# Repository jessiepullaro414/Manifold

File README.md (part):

# Manifold — KiCad schematic + PCB

Companion KiCad project for "Manifold", an Arduino Nano inspired (pinout/
form-factor only — not an official Arduino product, and not Arduino-IDE
compatible) 12V-powered board built from automotive/high-temp-rated parts
for engine-bay environments.

## Opening it

Open `Manifold.kicad_pro` in KiCad 6, 7, or 8. Everything the schematic needs
(all symbols) is embedded in `Manifold.kicad_sch` itself — no external symbol
libraries required to open and view it.

Both the schematic and `Manifold.kicad_pcb` are kept in KiCad's **current
native format** (not just an older-but-compatible one) — see "File format" below.

J1's footprint (TE AMPSEAL 776180-1) lives in this project too —
[`fp-lib-table`](fp-lib-table) registers it under the library nickname
`TE_AMPSEAL_776180-1`, pointing at [`footprints/TE_AMPSEAL_776180-1.pretty/`](footprints/TE_AMPSEAL_776180-1.pretty)
via `${KIPRJMOD}` (KiCad's "this project's folder" variable) — so it resolves
automatically for anyone who opens this project, without depending on where
it was originally downloaded to.

Same pattern on the schematic side: [`sym-lib-table`](sym-lib-table) registers
this project's own custom parts under the nickname `Manifold`, pointing at
[`Manifold.kicad_sym`](Manifold.kicad_sym) (both regenerated by `build_schematic.py` -
don't hand-edit either). The schematic still embeds every symbol inline too
(so it opens/nets fine even without this), but a real external library file
is what lets KiCad's own "Add Symbol" browser find `Manifold:*` parts, and is
what a from-scratch `kicad-cli sch erc` needs to not flag every single part
as "library not included in configuration".

## Building it

[`build.py`](build.py) runs the whole real pipeline in order — schematic
generation, PCB placement, autorouting, DRC — the same four scripts
described in "Routing it" and "How the schematic is built" below, just
chained together:

```
python build.py                 # full pipeline
python build.py --skip-route    # skip the slow FreeRouting pass
```

## Checking it

[`run_drc.py`](run_drc.py) runs `kicad-cli pcb drc` against `Manifold.kicad_pcb`
(or any other `.kicad_pcb` passed as an argument) and prints a readable report from
the JSON it produces — unconnected-item count (expected on this unrouted board) plus
every other violation type, grouped, with the actual offending items and positions,
not just per-type counts. `build_pcb.py` also runs DRC as its own last step, but only
prints counts; reach for this when you need the detail behind one of those counts.

```
python run_drc.py
python run_drc.py path/to/other.kicad_pcb
```

`kicad-cli sch erc Manifold.kicad_sch` is the schematic-side equivalent.
It went from **388 violations to 4** during a real triage pass (not just a
recount) - see "Rotated-footprint pad shapes" below and
[[kicad-file-generation-gotchas]] for the technical detail on each fix:

- 259 `endpoint_off_grid` - every symbol placement now snaps to KiCad's
  0.05in (1.27mm) schematic grid.
- 70 `lib_symbol_issues` - added a real `Manifold.kicad_sym` + `sym-lib-table`
  entry (this project's custom parts were only ever embedded inline in the
  schematic before, with no external library file backing them - fine for
  KiCad to open/net-list, not fine for its "library not found" check or for
  inserting a fresh instance from the symbol browser).
- 25 `label_dangling` + 25 `no_connect_connected` - U1's 25 spare MCU pins
  now get a real no-connect flag instead of a same-named, inherently
  one-off local label.
- 3 `isolated_pin_label` - same fix, applied to 3 individually-unused pins
  elsewhere (U2's PG, U4's NC, J2's NC) via a new `('nc',)` `place()` mode.
- 1 `pin_to_pin` - J1's +5V/+3V3 pins were typed `power_out` (implying the
  *connector* generates power), conflicting with U4's real LDO output on
  the same net - retyped `passive` (a connector pin exposing a rail isn't
  a second source of it).

**The remaining 4 are genuine, expected ERC characteristics, not bugs** -
each one is ERC's pin-type-based "is this driven?" check failing to trace
through a passive network or off-board source, not a real missing
connection:

- `+5V`, `VDDA`, and U2's `VIN` each show `power_pin_not_driven` because
  their real source sits on the far side of an LC filter (L1), a ferrite
  (L2), or a MOSFET (Q1) - none of which have a `power_out`-type pin to
  point to, since ERC doesn't trace continuity through passives.
- J2's `SWCLK` shows `pin_not_driven` because it's genuinely driven
  off-sheet, by an external debug probe.

If you regenerate and see anything **other than these same 4**, treat it
as a real regression, not baseline noise.

## Buck feedback divider - a real bug found in final review

R2/R3 (U2's FB divider) used to be 10k/3.3k, solving TI's own formula
(`Vout = VREF x (RFBT/RFBB + 1)`, VREF = 1V nominal per LMR33630-Q1's
datasheet Section 8.2.2.3) to **~4.03V, not 5V** - a real, roughly-1V-low
output, not a rounding nitpick. This mattered because that rail is exposed
on J1 as a Nano-compatible +5V pin for **external peripherals** - anything
expecting real 5V plugged into it would have been under-powered or
malfunctioned outright, and it ate into U4's LDO dropout margin too.

Fixed by solving for RFBB with RFBT held at 10k: `10k / (5V/1V - 1) = 2.5k`,
using the nearest standard E96 value, **2.49k** - which is suspiciously
exactly TI's own worked-example RFBB (24.9k, for their 100k/24.9k 5V
divider) scaled down by 10x, suggesting 3.3k was a substitution/typo
somewhere rather than a deliberate choice. New value gives ~5.02V.

## File format

`kiutils` (the library both generators use) writes the older v6-era schema by
default — version `20211014`, generator `kiutils`, unquoted UUIDs, no
`generator_version` field. KiCad opens that fine, but flags schematics as
needing conversion, and that would reappear every time either generator
regenerates its file.

Fixed at the source rather than worked around: both generators' last step
shells out to `kicad-cli sch upgrade` / `kicad-cli pcb upgrade` — KiCad's own
real format converter — on the file they just wrote. If `kicad-cli` isn't
found on your machine, the scripts still finish and print a note — the files
just won't be pre-upgraded.

## The PCB: what's real, what's placeholder, what's routed

[`build_pcb.py`](build_pcb.py) reads the schematic + a fresh `kicad-cli`
netlist export and generates `Manifold.kicad_pcb`: every part's **real**
footprint (loaded from its actual `.kicad_mod` file, not reinvented), with
every pad assigned the net the schematic says it should have.

**What this does NOT do: route copper.** Placement gives a compact starting
point, but this is a netlist-correct *unrouted* board — the same state
"Update PCB from Schematic" leaves you in before you route it yourself.

**Placement is a real 2D bin-pack, not a row of parts.** All 27 small parts
go through a single **skyline bin-packer**: it maintains a height profile
across the board's full width (fixed by J1 regardless of how tightly the
small parts pack — J1 is 20-40x bigger than everything else, so it, not the
small parts, sets the real width floor) and places each part wherever it
produces the lowest resulting top edge — trying *every* part both unrotated
and rotated 90°, not just a designated subset. Since greedy bin-packing is
order-dependent (which part gets considered first changes the whole
resulting layout), `best_skyline_pack` runs it with 5 different orderings
(largest-area, longest-side, tallest, widest, largest-perimeter first) and
keeps whichever actually produced the shortest board — cheap to do exhaustively
for 27 parts, and not something a single fixed heuristic can guarantee on
its own. Board is currently ~83×61mm, down from an initial ~142×88mm
row-based layout.

**Diminishing returns, checked quantitatively, not just eyeballed:** after
this rewrite, a per-mm-column height profile across the packed region shows
almost the *entire* width already sitting at or near the maximum height —
not one big rectangular gap like before, but a tightly-filled, slightly
uneven skyline. That's because U1 (the MCU - at the time, still the
placeholder LQFP48 footprint; see "U1's pinout" below for why that was
wrong and what replaced it) was 10.3×10.3mm — by far the single biggest
part — and its own footprint+margin
already accounts for most of the packed region's height on its own,
regardless of what gets stacked around it. Forcing U1 to place *last*
instead of first (an explicit experiment, not a guess) made the board
*worse* (21.0mm packed height vs. 13.6mm) because all the good low spots
were already taken by the time U1 needed one. Clustering the MCU's own
decoupling caps (100nF/1uF) physically next to it is genuinely good
practice for the real routed board's signal integrity, but in this
bounding-box model it wouldn't shrink the board further, since U1's own
footprint already sets the height floor no matter which parts sit next to
it.

**A second real bug, found by comparing against a manual rearrangement:**
after seeing this layout, the user manually spread the small-parts grid out
further in the KiCad GUI and saved the file - reading those exact saved
coordinates back out (`(at x y angle)` per footprint, regex-extracted since
kiutils can't re-parse a KiCad-saved file - see gotchas doc) showed their
arrangement using ~78mm of width to reach ~10.8mm of height, meaningfully
shorter than the script's own ~74.6mm-wide, ~12.2mm-tall result at the time.
The packer was handing itself less room than it actually had: `pack_width`
was `j1_width - 2*BOARD_MARGIN`, reserving a *second* margin on the right of
the small-parts grid on top of the margin baked into `board_width`'s own
`max(used_w, j1_width) + 2*BOARD_MARGIN` formula. Since board width is
already going to be at least `j1_width + 2*BOARD_MARGIN` regardless, giving
the packer up to the full `j1_width` costs nothing as long as it stays
within that - fixed by setting `pack_width = j1_width` outright. A width
sweep (72-95mm) confirms `j1_width` is the actual area-minimizing choice for
this part mix, not an arbitrary pick: going wider trims a little more
height but grows board width faster than that saves. Board dropped from
83.4×62.4mm to 83.4×61.0mm on this fix alone - free, since the board was
already going to be at least that wide.

The manual arrangement still edges out the automatic packer somewhat
(~10.8mm vs ~12.2mm content height) - most likely because a human doing
this by eye can look at the whole board and backtrack, where the packer
commits to each part's position in one greedy left-to-right pass and never
revisits it. Closing that remaining gap would need a fundamentally
different search (backtracking or exhaustive), not just another ordering
heuristic - tried 8 orderings x 11 width targets in a grid search and the
result barely moved (60.92mm best vs 61.0mm), confirming this is a real
plateau for the current greedy-heuristic family, not a tuning oversight.

This replaced an earlier two-block design (a fixed "actives" column next to
a "caps" grid, sized by a pre-computed proportional-area split, with small
headers optionally dropped into whatever rectangle the split left over).
That design couldn't reach real density: caps are small and uniform and
pack far more efficiently per mm² than the actives, so even a "correct"
area-proportional width split still left the caps block *shorter* than the
actives column, and the leftover rectangle only fit parts that happened to
match its exact shape — real open board space stayed open, which is exactly
what got flagged when reviewing a render. A single shared skyline profile
lets any part drop into any low spot next to any neighbor, not just its own
block's slice, which is what actually closes gaps like that.

**A real rotation bug was caught verifying this one.** The 90°-CCW local
coordinate transform `(x,y) → (-y,x)` used everywhere rotation was needed —
in the packer's own placement math *and* in the pre-write overlap-check
verification, so both sides agreed with each other — turned out to be
backwards for KiCad's actual rotation direction (`(x,y) → (y,-x)`). Because
both sides used the same wrong formula, the script's own overlap assertion
never caught it — it was internally consistent, just wrong. It surfaced
instead as a real, tiny (0.015-0.18mm) pad-to-pad `clearance` and
`shorting_items` DRC violation between a rotated pin header (J3) and a
neighboring IC (U2), where the rotated header's far pads landed almost on
top of the IC's pads instead of facing away from it. Confirmed by manually
computing where kicad-cli's real DRC said those specific pads actually were,
which only matched the `(y,-x)` transform. This is the reason bugs like this
get caught by `kicad-cli`'s real DRC and not just the script's own geometry
checks — two internally-consistent code paths agreeing with each other is
not the same as either of them being correct.

Three more real bugs were found and fixed while doing this work:

- **Footprint bounding boxes were pad-only**, undercounting parts like J1 —
  a right-angle through-hole connector whose silkscreen/body outline extends
  well past its pad positions. This produced margins that looked fine on
  paper but caused real `silk_edge_clearance` and `courtyards_overlap` DRC
  errors at tight spacing. Fixed by including silkscreen graphics (lines,
  polys, arcs) in the bbox calculation, not just pads — after which margins
  could go back down to their intended tight values and every clearance
  error disappeared.
- **Every part showed as "REF\*\*"** in DRC reports and the 3D viewer,
  because only the silkscreen *text* was being updated (`fp.graphicItems`),
  not the separate `fp.properties["Reference"]`/`["Value"]` dict that KiCad's
  own tools (DRC, BOM, 3D view) actually read from. Fixed by setting both.
- **Every reference designator sat dead center on its own part, on top of
  its own pads** (`silk_over_copper` x58, `silk_overlap` x35 in
  `kicad-cli pcb drc` - see [run_drc.py](run_drc.py) below). Root cause:
  kiutils' `Footprint.properties` is a plain `{name: value}` string dict - it
  has no field for a property's position, layer, or font, so `to_file()` can
  only ever write a bare `(property "Reference" "REF")` token, discarding
  whatever real position the *source* library footprint had. `kicad-cli pcb
  upgrade` then fills in the missing fields using KiCad's own built-in
  default *for that property name* - Reference defaults to `(at 0 0 0)` on
  `F.SilkS`, i.e. dead center - which is fine on a normally-spaced board but
  guarantees overlap at this board's 2mm part spacing. (Value/Datasheet/
  Description bare properties *don't* show up as silkscreen violations,
  because KiCad's defaults for those names are F.Fab/hidden, not visible
  silkscreen - so this was specifically a Reference-designator problem, not
  a general "properties are broken" problem.) Fixed by patching the written
  file's bare `(property "Reference" "REF")` tokens - exact string
  replacement, not regex, since the one-line form kiutils writes is exactly
  known at that point in the script, before `pcb upgrade` ever touches the
  file - with a real per-part position (just clear of that part's own bbox,
  reusing the same `footprint_bbox()` already used for placement) and a
  0.8mm font sized for 2mm part spacing instead of KiCad's normal 1.27mm
  default. Went from 96 DRC violations to 3 (the remaining 3 are an
  unrelated `lib_footprint_mismatch` finding - local footprint copies
  differing slightly from their library originals, not a silkscreen issue).

## Layer stackup: 4 layers

`board.layers` now declares `F.Cu`, `In1.Cu`, `In2.Cu`, `B.Cu` (verified
present in the generated file after `pcb upgrade`). In1 as a solid GND pour
and In2 as a +5V/+3V3 pour is standard practice for a board with a switching
buck regulator on it — shorter return paths, better EMI — and this board
already has one, so 4 layers is a sensible default rather than an arbitrary
choice. Exact dielectric thickness/material is left at KiCad's defaults; set
those in Board Setup if you have fab-specific requirements.

**The planes are now real, not just planned.** `route_board.py`'s
`add_and_fill_zones()` pours a solid **GND zone on In1.Cu** and a solid
**+3V3 zone on In2.Cu** (the primary MCU supply rail now that U1 runs
entirely on 3.3V — see "The MCU" below; +5V stays a normal routed trace,
since it's the lower-current Nano-compatibility rail feeding just J1's +5V
pin and the LDO input, not something else on this board depends on for a
low-impedance return path the way the buck regulator's GND loop does).

**Zones are added AFTER routing, not before — that ordering is load-bearing,
not a style choice.** The first attempt added the zone outlines in
`build_pcb.py`, *before* handing the board to FreeRouting, on the theory
that its Specctra DSN "plane" mechanism would let the autorouter treat
those layers as pre-claimed and route everything else around them. That
backfired two different ways:

1. **It made this already-tight board measurably harder to autoroute.** A
   solid zone covering an entire inner layer removes that layer's normal
   "just drop a via here" flexibility everywhere on the board, not only
   where the plane's own net actually needs it — and this board has a
   0.5mm-pitch 64-pin LQFP and a similarly tight VQFN-12 with very little
   room to spare already. Runs that reliably hit 0 unrouted nets before
   zones existed started leaving 1-4 stuck on the same few tight spots
   (U2's exposed-pad-to-pin connection, some U1-to-J1 nets) with zones
   present pre-route.
2. **Worse: FreeRouting would report "100% routed" while `run_drc.py` still
   found real "missing connection" findings** between GND/+3V3 pads (e.g.
   J1's THT pins) and the zone itself. The router had skipped drawing an
   explicit trace/via to some pads, assuming the plane would cover them —
   but the *actual* fill polygon, computed afterward and cleared around
   every other net's copper, didn't always reach every such pad. FreeRouting's
   own self-report and KiCad's real DRC were checking two different things,
   and only the second one is trustworthy — another instance of this
   project's running theme that a tool's own "success" claim isn't
   verification.

The fix: route the whole board as ordinary traces first — the same simple,
reliable regime that got 0 unconnected items before any zones ever existed —
and only *then* add the zones as purely additive copper on top of an
already-100%-connected board. Any GND/+3V3 trace or via the zone happens to
overlap becomes redundant (harmless), not the *only* connection, so there's
no longer any way for a pad to end up "connected only via a plane that
doesn't quite reach it." Pad connections are solid (`ZONE_CONNECTION_FULL`),
not thermal-relief spokes, for the same reliability reason — no spoke
geometry to fail, and this board isn't hand-soldered at a scale where
thermal relief's easier-rework benefit outweighs connection certainty.

**One more real bug along the way, a KiCad Python-scripting one, not a
design one:** filling both zones (different layers) in a single `pcbnew`
process reliably **segfaults** on the subsequent `board.Save()` — confirmed
directly by isolating each step (adding both zones: fine; filling both:
fine; only `Save()` afterward crashes, every time, only with two
different-layer zones present together). One zone filled and saved alone
never crashes. Root cause looks like a real threading/state bug in this
KiCad build's zone filler under scripting, not something to tune around via
zone settings — worked around by doing each zone in its own **separate**
`python.exe` subprocess (load → add one zone → fill → save), so the second
zone's process loads a file that already has the first zone's completed
fill baked in, and the two fills are never in memory together.

## Branding: the JessiesCars logo on B.SilkS

`build_pcb.py` places a real vector logo (badge + winged mark) on the back
silkscreen, sourced from [`both.kicad_sym`](both.kicad_sym) — a
`bitmap2component`-generated schematic symbol (29 polylines, ~1450 points,
traced from the real artwork, not anything this script invents). B.SilkS is
otherwise completely empty (nothing's mounted on the back), so it's placed
in J1's own footprint "shadow" — J1's bbox has a tall lower region below its
3 pad rows (its plastic housing outline) with zero pads or drills in it,
genuinely clear space rather than just visually-empty space a THT pad barrel
would poke through.

**Two coordinate-transform bugs, both caught by literally looking at the
render, not by DRC** (DRC has no way to know a logo is upside down or
backwards — this is a visual-correctness class of bug, not an electrical
one):

1. **Symbol space is Y-up, PCB board space is Y-down** — the exact same
   convention gotcha `build_schematic.py` already documents for placing
   symbol pins onto the sheet, easy to forget applies here too since
   `both.kicad_sym` is *also* a symbol-space file. Missing this flip put the
   whole logo upside down on the first attempt.
2. **A back-layer shape's stored coordinates are NOT auto-mirrored by
   KiCad** — only *text* gets a `mirror` flag (`Justify(mirror=True)`, see
   `kicad-file-generation-gotchas`); a plain polygon's points are used
   as-is, so artwork authored in normal (front-view) orientation reads
   backwards once the physical board is flipped over to view the back. Text
   needs the flag; polygons need their X coordinates negated by hand before
   placing, since they have no equivalent flag to set.

Both flips are real and both apply *together* (not either/or) — applying
only one produces a result that's wrong in a *different*, less obviously
"just mirrored" way (a 180° rotation, not a clean left-right flip), which is
exactly what the first attempt looked like: legible-ish but wrong letters
("CARZ" for "CARS"), not obviously backwards at a glance. Fixed by negating
*both* X and Y before scaling/placing. Verified by rendering the back side
(`kicad-cli pcb render --side bottom`) and reading the actual wordmark, not
just checking DRC — DRC-clean and visually-correct are different checks
here.

Same `gr_poly` gotcha as `gr_text` on the uuid front: kiutils' `tstamp`
field writes an unquoted `(tstamp xxxx)`, not the quoted `(uuid "xxxx")` a
real KiCad-written `gr_poly` has, and `kicad-cli` segfaults loading the file
without it — patched post-write, same pattern as the Reference-label and
credit-text fixes before it.

## Routing it

[`route_board.py`](route_board.py) routes the board with
[FreeRouting](https://github.com/freerouting/freerouting), the same way most
KiCad users do it manually: export a Specctra `.dsn`, autoroute it, import
the resulting `.ses` back, then pour the GND/+3V3 zones on top. Four steps,
run headless:

```
python route_board.py
python run_drc.py
```

1. **Export** — `pcbnew.ExportSpecctraDSN()`, called through KiCad's own
   *bundled* Python (`C:\Program Files\KiCad\10.0\bin\python.exe`, which has
   the real `pcbnew` module — different from the Python that runs the rest
   of this project's scripts). This is KiCad's real, tested exporter, not a
   reimplementation — `kicad-cli` doesn't expose DSN export at all (checked;
   its `pcb export` subcommand list has no `dsn`/`specctra` option), but the
   underlying scripting API does, and it's fully headless.
2. **Route** — `java -jar tools/freerouting-2.2.4.jar -de ... -do ... -mp 60
   -oit 0 --gui.enabled=false`. Requires Java (this project uses Eclipse
   Temurin 25 JRE) and the FreeRouting jar (57.8MB, not committed — see
   below).
3. **Import** — `pcbnew.ImportSpecctraSES()`, same bundled-Python mechanism,
   writes the routed tracks/vias back into `Manifold.kicad_pcb` and
   saves it.
4. **Pour zones** — GND on In1.Cu, +3V3 on In2.Cu, added and filled *after*
   routing (not before — see "Layer stackup" above for why that ordering
   matters and the real bugs skipping it caused), each in its own separate
   `python.exe` subprocess (also explained above — filling both in one
   process segfaults on save).

**Setup** (one-time): install a JRE, and download
[`freerouting-2.2.4.jar`](https://github.com/freerouting/freerouting/releases/tag/v2.2.4)
into `tools/`. The **jar**, not the installer — FreeRouting's own docs
specify the jar for headless/CLI use; the installers are for interactive
use only.

**Current result**: FreeRouting routes all 47 nets (103 pin-to-pin
connections, after U1's real 64-pin pinout replaced the old unwired
placeholder — see "U1's pinout" below) in 15-30 seconds — `run_drc.py`
confirms 0 unconnected items, same handful of pre-existing
`lib_footprint_mismatch` findings as before, nothing routing-related.

**The autorouter isn't perfectly deterministic run-to-run** — occasionally
it'll settle for 1-4 nets unrouted and stop (its own plateau-detection
gives up when a pass makes no further progress), rather than reaching 0
every single time. When that happens, just re-run `python route_board.py`
from a fresh `python build_pcb.py` (not on top of the partially-routed
board — re-routing incrementally on top of a stuck partial state hits the
same plateau again, since nothing about the board actually changed).
A second full-from-scratch attempt has reliably reached 0 unrouted so far.

**The inner layers are real planes now, not general routing layers** — see
"Layer stackup" above for the GND/+3V3 zone pours and the real bugs (a
routing-reliability regression and a scripting segfault) that showed up
getting there.

**U1 is fully wired now — no exceptions.** Earlier revisions of this board
left every one of U1's pads without a net, because its schematic pin numbers
were an unverified generic placeholder that didn't reflect any real chip's
actual pinout — wiring them to the real footprint's pads by number
coincidence would have produced confidently *wrong* connections, worse than
no connections at all. That's resolved: U1's pin numbers are now the real,
NXP-Reference-Manual-verified S32K144 64-pin LQFP pinout (see "U1's pinout"
above), so it gets normal net assignment like every other part.

Verified after generation, every time: no two footprints' bounding boxes
overlap, every net has the same pin count on the PCB as in the schematic (47
nets currently), and a real `kicad-cli pcb drc` pass comes back with zero
connectivity/footprint errors (only a benign "doesn't match library copy"
metadata nag on a handful of footprints that's just an artifact of embedding
them via script — re-running "Update Footprints from Library" in pcbnew
clears it).

**A real bug caught and fixed during this verification:** the AMPSEAL
connector's downloaded footprint uses KiCad's legacy *unquoted* pad-number
syntax, which `kiutils` parses as a Python `int` — silently failing every
net-lookup for that footprint (all pad numbers are stored as strings
everywhere else) until the lookup was fixed to normalize types. Before the
fix, J1 looked structurally fine (right pad count, right pattern) but
carried zero of its real net assignments.

## How the schematic is built

Every part uses a **generic placeholder symbol**: a rectangle body with pins.
For most parts (see below), the pin count/numbers/names are now **real**,
verified against actual manufacturer datasheets — not generic filler.

Connectivity uses three mechanisms, matching normal schematic practice:

- **Drawn wires** for the main signal flow: the 12V power chain (fuse →
  reverse-battery FET → buck), the MCU↔J1 signal bus, and the crystal.
- **Power symbols** (+5V, +3V3, GND, VIN) at every power-net connection point.
  Power nets deliberately never use local labels — mixing local labels with
  power symbols splits nets in KiCad.
- **Local labels** for shared or non-Nano-pinout signals: UART sharing D0/D1,
  the FB divider, VDDA/AREF/OSC taps, VCAP/BOOT_CAP for the two ICs that need
  an external charge-pump/bootstrap cap.

**Before you route a board from this:** swap the placeholder symbols for real
library symbols (matching what's now real about the footprints/pinouts) and
give it a visual tidy-up. Treat this as a correct **netlist and BOM skeleton**,
not a finished, review-ready schematic.

## Sections on the sheet

| Section | Refs | Notes |
|---|---|---|
| Power input & protection | F1, Q1, U3, D1, C1, C10 | Fuse, reverse-battery ideal-diode + FET, TVS clamp, charge-pump cap |
| 5V buck regulator | U2, L1, C2, R2, R3, C11, C12 | 12V (9–40V transient) → 5V. Now exists **only** for a Nano-compatibility 5V pin on J1 — the MCU itself no longer runs on this rail |
| 3.3V LDO | U4, C3 | Steps 5V → 3.3V, which is now the **primary MCU supply**, not just a spare pin |
| MCU core | U1, Y1, C4–C5, L2, R1 | NXP S32K144 automotive (real AEC-Q100 qualification), 8MHz placeholder crystal, reset pull-up, VDDA ferrite-filtered |
| Connectors | J1, J2, J3 | J1 = full Nano-pinout I/O on a **TE AMPSEAL 776180-1** (35-pos, right-angle, sealed), J2 = **SWD** (SWDIO/SWCLK/RESET), J3 = UART (shares D0/D1) |

Full component rationale lives in the design-spec document delivered
alongside this file — this schematic is the follow-through on that spec.

## The MCU: from ATmega328P → STM32 → NXP S32K144 (and losing "Arduino IDE")

This went through two real revisions, both driven by things that turned out
not to be true on closer inspection:

1. **ATmega328P → STM32L452xx**, because no automotive-qualified 5V-native
   Arduino-ish chip exists. This looked right at the time.
2. **STM32L452xx → NXP S32K144**, because it turned out mainstream STM32
   (Cortex-M) parts have **no AEC-Q100 qualification at all** — confirmed via
   ST's own community forum: *"not a single device in the standard STM32
   family meets the AEC-Q specs."* ST's real automotive 32-bit line (SPC5) is
   Power Architecture, not ARM, not Arduino-anything.

NXP's S32K1 family is genuinely AEC-Q100 qualified Arm Cortex-M4F. But:

- **This means giving up Arduino IDE support entirely** — not just the
  STM32duino alias-mapping caveat from before. NXP's own S32K144 EVB
  documentation is explicit: *"the NXP S32K144 is NOT natively supported by
  the Arduino IDE... development requires the dedicated S32 Design Studio IDE
  and the S32 Software Development Kit."* The "Arduino UNO pin layout"
  compatibility NXP markets is **physical only** — no `digitalWrite()`,
  `Serial`, or sketch-based workflow exists for this chip. Programming is via
  NXP's Eclipse-based IDE and an AUTOSAR-style SDK — a genuinely different,
  more automotive-industrial development workflow.
- **Still 3.3V logic, not 5V** — same consequence as before, unrelated to
  which 3.3V-logic chip is on the board. J1's dedicated +5V pin (unconnected
  to the MCU) remains the only genuine 5V on the board.

### U1's pinout: from placeholder to real, verified, and fully wired

**The 48-pin LQFP placeholder used until now was not just unverified — it
was wrong.** The S32K144 does not come in a 48-pin LQFP package at all.
Confirmed three independent ways against NXP's own S32K1xx Series Reference
Manual (Rev 8, 06/2018): S32K144's own pin-mapping sheet only has columns
for 64-LQFP/100-LQFP/100-BGA; sibling part S32K142's sheet is the same;
48-pin LQFP is a real NXP package, but it belongs to the smaller
S32K116/S32K118 sub-family (Cortex-**M0+**, not the M4F this board was
chosen for). **The real minimum package for S32K144 is 64-pin LQFP.**

Every earlier attempt at this (this session and prior ones) failed to fetch
the "pin table" because it isn't in the datasheet or Reference Manual's
visible text at all — NXP ships it as a spreadsheet
(`S32K144_IO_Signal_Description_Input_Multiplexing.xlsx`) embedded as a PDF
**file attachment** inside the Reference Manual, not as text or a table on
any page. Regular PDF text extraction (`pdftotext`, WebFetch) can't see it.
Pulled out directly with `pypdf`'s attachment API once a mirror that wasn't
blocking the download was found (Farnell, not Mouser/NXP/community.nxp.com —
all three of those still 403/timeout).

With the real, verified 64-pin table in hand, **U1 is now fully wired** —
no more placeholder, no more unwired pads:

- **58 real GPIO pins**, of which 5 keep their real default (reset-state)
  function matching how this board already used them: pin 11 (PTB7/EXTAL)
  and 12 (PTB6/XTAL) → the crystal, pin 62 (PTC4/SWD_CLK) and 64
  (PTA4/SWD_DIO) → the SWD header, pin 63 (PTA5/RESET_b) → reset.
- **VREFH (pin 9, the real ADC voltage-reference pin) goes to J1's AREF** —
  not a placeholder GPIO. AREF on a real board should reach the actual
  reference input, and now it does.
- **D0–D19 (20 pins, up from the placeholder's 14)** and **A0–A7 (8 pins,
  specifically chosen from the 27 real GPIO pins with a genuine `ADCn_SEx`
  alternate function — "analog in" is a real capability here, not just a
  name carried over from Arduino)**. D14–D19 are new: J1's 6 previously-spare
  pins now carry them, so **all 35 of J1's positions are used, zero spare**
  (see "Nano-pinout I/O" below).
- The other **25 free GPIO pins** aren't wired to anything — J1 has no more
  physical positions left for them — and are marked `no_connect` on the
  schematic with their real pin numbers, not placeholder ones.
- **U1's PCB footprint is now the real bundled KiCad
  `Package_QFP:LQFP-64_10x10mm_P0.5mm`**, replacing the placeholder
  `LQFP-48_7x7mm_P0.5mm`. `build_pcb.py`'s old "leave U1 unwired, its pin
  numbers might be wrong" special case is gone — U1 gets normal net
  assignment like every other part now, because its pin numbers are real.

SWDIO/SWCLK were always real, universal Arm Cortex-M debug signals
regardless of vendor — that part of the old placeholder note held up.
There is no BOOT0-style pin on this family (that was STM32-specific).

## Four parts that got real, verified pinouts this session

While researching the MCU footprint, real datasheet research (TI and
Nexperia PDFs, pulled and parsed directly) turned up genuine errors in four
other parts — now fixed with real pin numbers, not generic placeholders:

- **U2 (buck regulator):** LMR33630-Q1's real package is **VQFN-HR-12
  ("RNX0012C", 2×3mm body, ≤1mm height)** — it was never offered in
  HTSSOP-16 at all, which is what the schematic originally specified. Real
  12-pin table verified against TI's datasheet Table 5-1: symmetric
  VIN/PGND pairs for EMI cancellation, NC(3) tied to SW per the datasheet's
  own instruction, BOOT(4) needs a cap to SW (added: C11), VCC(5) is an
  internal 5V rail needing its own decoupling cap (added: C12), PG(8)
  unused here. **This package has no exposed pad at all** — an earlier
  version of this file (and the schematic) had a 13th "EP" pin tied to
  GND, which was wrong and has been removed; TI's own Pin Functions table
  has no EP row for this variant. The footprint is custom-built (not a
  bundled KiCad part, and not the wrong-sized 4×4mm placeholder used
  earlier) — see [`build_u2_footprint.py`](build_u2_footprint.py) for how
  the land pattern was derived directly from TI's package drawing
  (4225021/C, 05/2022) and [`footprints/TI_RNX0012C_VQFN-HR.pretty/`](footprints/TI_RNX0012C_VQFN-HR.pretty)
  for the result. This package's pin layout is genuinely irregular — 4
  pins down each side, 3 along the bottom, and one larger single pin (SW)
  on its own at the top — not a simple 3-per-side QFN, so it's worth
  opening the footprint in KiCad's footprint editor at least once before
  fab to see the real shape.
- **U3 (ideal-diode controller):** the schematic originally specified
  **LM74670-Q1, which turned out to be the wrong part** — that's TI's
  controller for alternator/rectifier diode emulation, not reverse-battery
  protection. The correct, purpose-built part is **LM74700-Q1** ("Low IQ
  Reverse Battery Protection Ideal Diode Controller"), real 6-pin SOT-23
  (DBV) package, real pinout verified against TI's datasheet. It also needs
  an external charge-pump capacitor across VCAP and ANODE that the schematic
  never had — added as C10, now confirmed at **100nF** against TI's actual
  design guidance (section 10.1.1.2.3): "VCAP: Minimum 0.1uF is required;
  recommended value of VCAP(uF) >= 10 x CISS(MOSFET)(uF)". Q1's real Ciss
  (450pF for the current part, PMV37ENEA, per Nexperia's datasheet) makes
  the formula's own figure (4.5nF) far smaller than the flat 0.1uF minimum,
  so the minimum governs - matching TI's own 12V-battery-protection example
  circuit exactly. The original 10nF value was 10x under TI's stated
  minimum, not just an unconfirmed guess.
- **U4 (LDO):** real candidate **TLV733P-Q1** (AEC-Q100) is 5-pin SOT-23
  (DBV), not the 3-pin package originally assumed. Real pinout verified
  against TI's datasheet.
- **Q1 (MOSFET), resolved with a real part swap:** the original candidate,
  **Nexperia PMV230ENEA** (AEC-Q101, SOT-23, pinout Gate=1/Source=2/Drain=3,
  verified against Nexperia's datasheet), derated to 0.9A at 100°C ambient -
  genuinely *below* F1's fuse rating at the time (originally 1A - see "F1"
  below for why it's now 2A), meaning the MOSFET could overheat at F1's
  normal, non-fault operating current, not just a thin margin. Replaced with
  **PMV37ENEA**: same SOT-23/TO-236AB package, same pinout, same 60V VDS (no
  TVS/clamping rework needed) - but RDSon of 37-49mOhm (vs 176-222mOhm)
  gives 3.5A@25°C / **2.5A@100°C**, comfortably above F1's rating with real
  margin either way (1A originally, 2A now), AEC-Q101 qualified, -55 to
  175°C range. One minor, honestly-noted mismatch: PMV37ENEA's max Vth
  (2.7V) is slightly above LM74700-Q1's own stated preference ("2V to 2.5V
  maximum") for its light-load regulation scheme - not a hard limit, worth
  a bench check at light load before final part lock.

A real geometry bug was also caught and fixed while wiring these up: a GND
power connection's extra riser wire landed exactly on a neighboring pin's own
stub, silently shorting that pin's real net onto GND. Caught via `kicad-cli`
netlist diff (an entire net had vanished), fixed, and now checked
automatically on every regeneration (`build_schematic.py` asserts no two
different net labels ever land on the same coordinate).

## AEC-Q100 / Q101 / Q200 grade key

Every part's `Value` field on the sheet is tagged with its actual automotive
qualification:

- **Q100 G1** = AEC-Q100 Grade 1 (−40°C to 125°C) for *integrated circuits*:
  U2 (buck), U3 (ideal-diode controller), U4 (LDO) — all TI, all verified.
  U1 (MCU) carries **AEC-Q100** (no grade suffix, since the exact grade for
  this NXP family wasn't independently confirmed this session).
- **Q101** = AEC-Q101, for *discrete semiconductors*: Q1 (MOSFET), D1 (TVS).
- **Q200** = AEC-Q200, for *passives*: Y1, C1–C13, R1–R3, L1, L2.
- **F1 (fuse) and J1–J3 (connectors) intentionally have no AEC-Q tag** — those
  categories aren't covered by the AEC-Qxxx family at all; they're qualified
  against their own standards (SAE J2077 / ISO 8820-3 for F1's real Littelfuse
  297 MINI automotive blade fuse, connector-specific automotive standards for
  J1-J3). Don't read the missing tag as an oversight.

## Footprints (for "Update PCB from Schematic")

Every footprint field is a real KiCad library reference, checked directly
against the actual `.kicad_mod` files (not just typed from memory):

- F1: Keystone 3568 Mini blade fuse holder (`Fuse:Fuseholder_Blade_Mini_Keystone_3568`,
  bundled directly in KiCad, 3D model included) - a traditional, physically
  replaceable automotive blade fuse, not a soldered-down SMD fuse. See
  "F1: traditional blade fuse" below for why.
- U2: real, custom-built VQFN-HR-12 footprint (`TI_RNX0012C_VQFN-HR:TI_RNX0012C_VQFN-HR-12_2x3mm_P0.5mm`)
  — see above and [`build_u2_footprint.py`](build_u2_footprint.py).
- U3: real SOT-23-6 (bundled).
- U4: real SOT-23-5 (bundled).
- Q1: real SOT-23 (bundled).
- J2: `Tag-Connect_TC2030-IDC-NL...` — note the hyphen KiCad's real file uses
  (`Tag-Connect`, not `TagConnect`).
- **J1 is fully resolved, including a real dimensional check:** **TE
  Connectivity AMPSEAL 776180-1** — 35-position, 3-row, 4mm pitch,
  right-angle through-hole, sealable, −40°C to 125°C / IP67. Its footprint
  was downloaded from
  [SnapEDA](https://www.snapeda.com/parts/776180-1/TE+Connectivity/view-part/)
  and copied into [`footprints/TE_AMPSEAL_776180-1.pretty/`](footprints/TE_AMPSEAL_776180-1.pretty)
  for project portability. Checked directly against TE's own real customer
  drawing (`ENG_CD_776180_J.pdf`, fetched from `te.com`'s document-delivery
  system, sheet 2's "RECOMMENDED P.C. BOARD LAYOUT" - a real, dimensioned
  engineering drawing, not the datasheet's summary page): pin drill
  (Ø1.75mm), pin pitch (4mm), row stagger (2mm), mounting-hole diameter
  (Ø2.85mm), and mounting-hole-to-mounting-hole span (57mm) all matched the
  downloaded footprint exactly. **One real, genuinely wrong dimension was
  found and fixed**: the two non-plated mounting holes were 0.5mm off in Y
  (at 4.5mm instead of 4.0mm) - TE's drawing shows them sitting exactly
  in-line with the middle pin row, not offset from it. Confirmed via the
  PDF's own vector geometry (mounting hole's crosshair falls exactly on the
  middle row's construction line), not just eyeballing the rendered page.
  Fixed directly in `TE_1-776180-1.kicad_mod` (a downloaded static library
  asset, not something this project's scripts generate from scratch, so a
  direct edit - not a generator script - is the right fix here).
- **U1 is fully resolved too** — see "U1's pinout" above. The footprint
  *was* the issue here (LQFP48 isn't a real S32K144 package at all), not
  just the pin-to-net mapping; both are fixed now, using the real
  Reference-Manual-verified 64-pin LQFP pinout and footprint.

## 3D models

Four parts had no 3D model showing in KiCad's 3D viewer, for three
different reasons:

- **J1** simply never had one — its footprint was a bare SnapEDA download
  (2D only). Fixed with a real manufacturer STEP file
  ([`1-776180-1.step`](footprints/TE_AMPSEAL_776180-1.pretty/TE_1-776180-1.step)),
  downloaded and supplied directly by the user, wired into
  `TE_1-776180-1.kicad_mod` with a `${KIPRJMOD}`-relative `(model ...)`
  block (same portability pattern as the footprint itself).
- **F1** (originally the Littelfuse NANO2 SMD fuse) had this same missing-
  model problem — its `(model ...)` reference pointed at
  `${KICAD10_3DMODEL_DIR}/Fuse.3dshapes/Fuse_Littelfuse-NANO2-451_453.step`,
  which doesn't actually exist in this KiCad 10 install (checked directly:
  the real `Fuse.3dshapes` folder has 28 files, none of them this one) - a
  real packaging gap in the bundled library, not a project bug. Moot now:
  F1 was later replaced entirely with a traditional Mini blade fuse holder
  (see "F1: traditional blade fuse" below) whose bundled model genuinely
  exists in this install, so no placeholder/workaround is needed for F1
  anymore at all.
- **U2**'s custom-built footprint (see above) never had a model at all,
  since it was hand-built from a datasheet rather than downloaded from a
  library that would normally ship one alongside it.
- **J2** (Tag-Connect TC2030-IDC-NL) is not a bug and got no model: its
  real footprint (checked directly against the bundled `.kicad_mod`) is 6
  bare `connect`-type pads plus 2 non-plated locating holes and nothing
  else — `attr exclude_from_pos_files exclude_from_bom` even marks it as
  not a placeable, orderable part. The actual Tag-Connect hardware is a
  detachable pogo-pin cable head that's never mounted on the assembled
  board, so there's genuinely no physical body to model here.

U2's placeholder ([`build_3d_models.py`](build_3d_models.py), using
[`cadquery`](https://cadquery.readthedocs.io/) to write a real STEP file, not
just a KiCad-only format) is a real-dimension bounding box, not
manufacturer-exact art — good enough for a 3D-viewer sanity check and
clearance reasoning, not a photorealistic BOM render:

- U2: 2.0 x 3.0 x 1.0mm, the same real TI package-drawing dimensions
  already used to build the 2D footprint (`build_u2_footprint.py`).

## Rotated-footprint pad shapes (real KiCad/kicad-cli characteristic, not a script bug)

Building U2's real, densely-pitched (0.5mm) VQFN-HR footprint surfaced a
subtle, reproducible characteristic of how KiCad 10.0.4 handles a footprint
placed at a 90° rotation: the footprint's overall placement rotation (its
`(at x y 90)`) correctly rotates every pad's *position*, but does **not**
carry through to each pad's own *shape* for rendering or DRC purposes unless
that pad also has its own local rotation angle set to match. Confirmed with
a from-scratch, hand-written two-pad test footprint (no `kiutils` involved
at all) placed once at 0° and once at 90°: only the 90° copy showed a false
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
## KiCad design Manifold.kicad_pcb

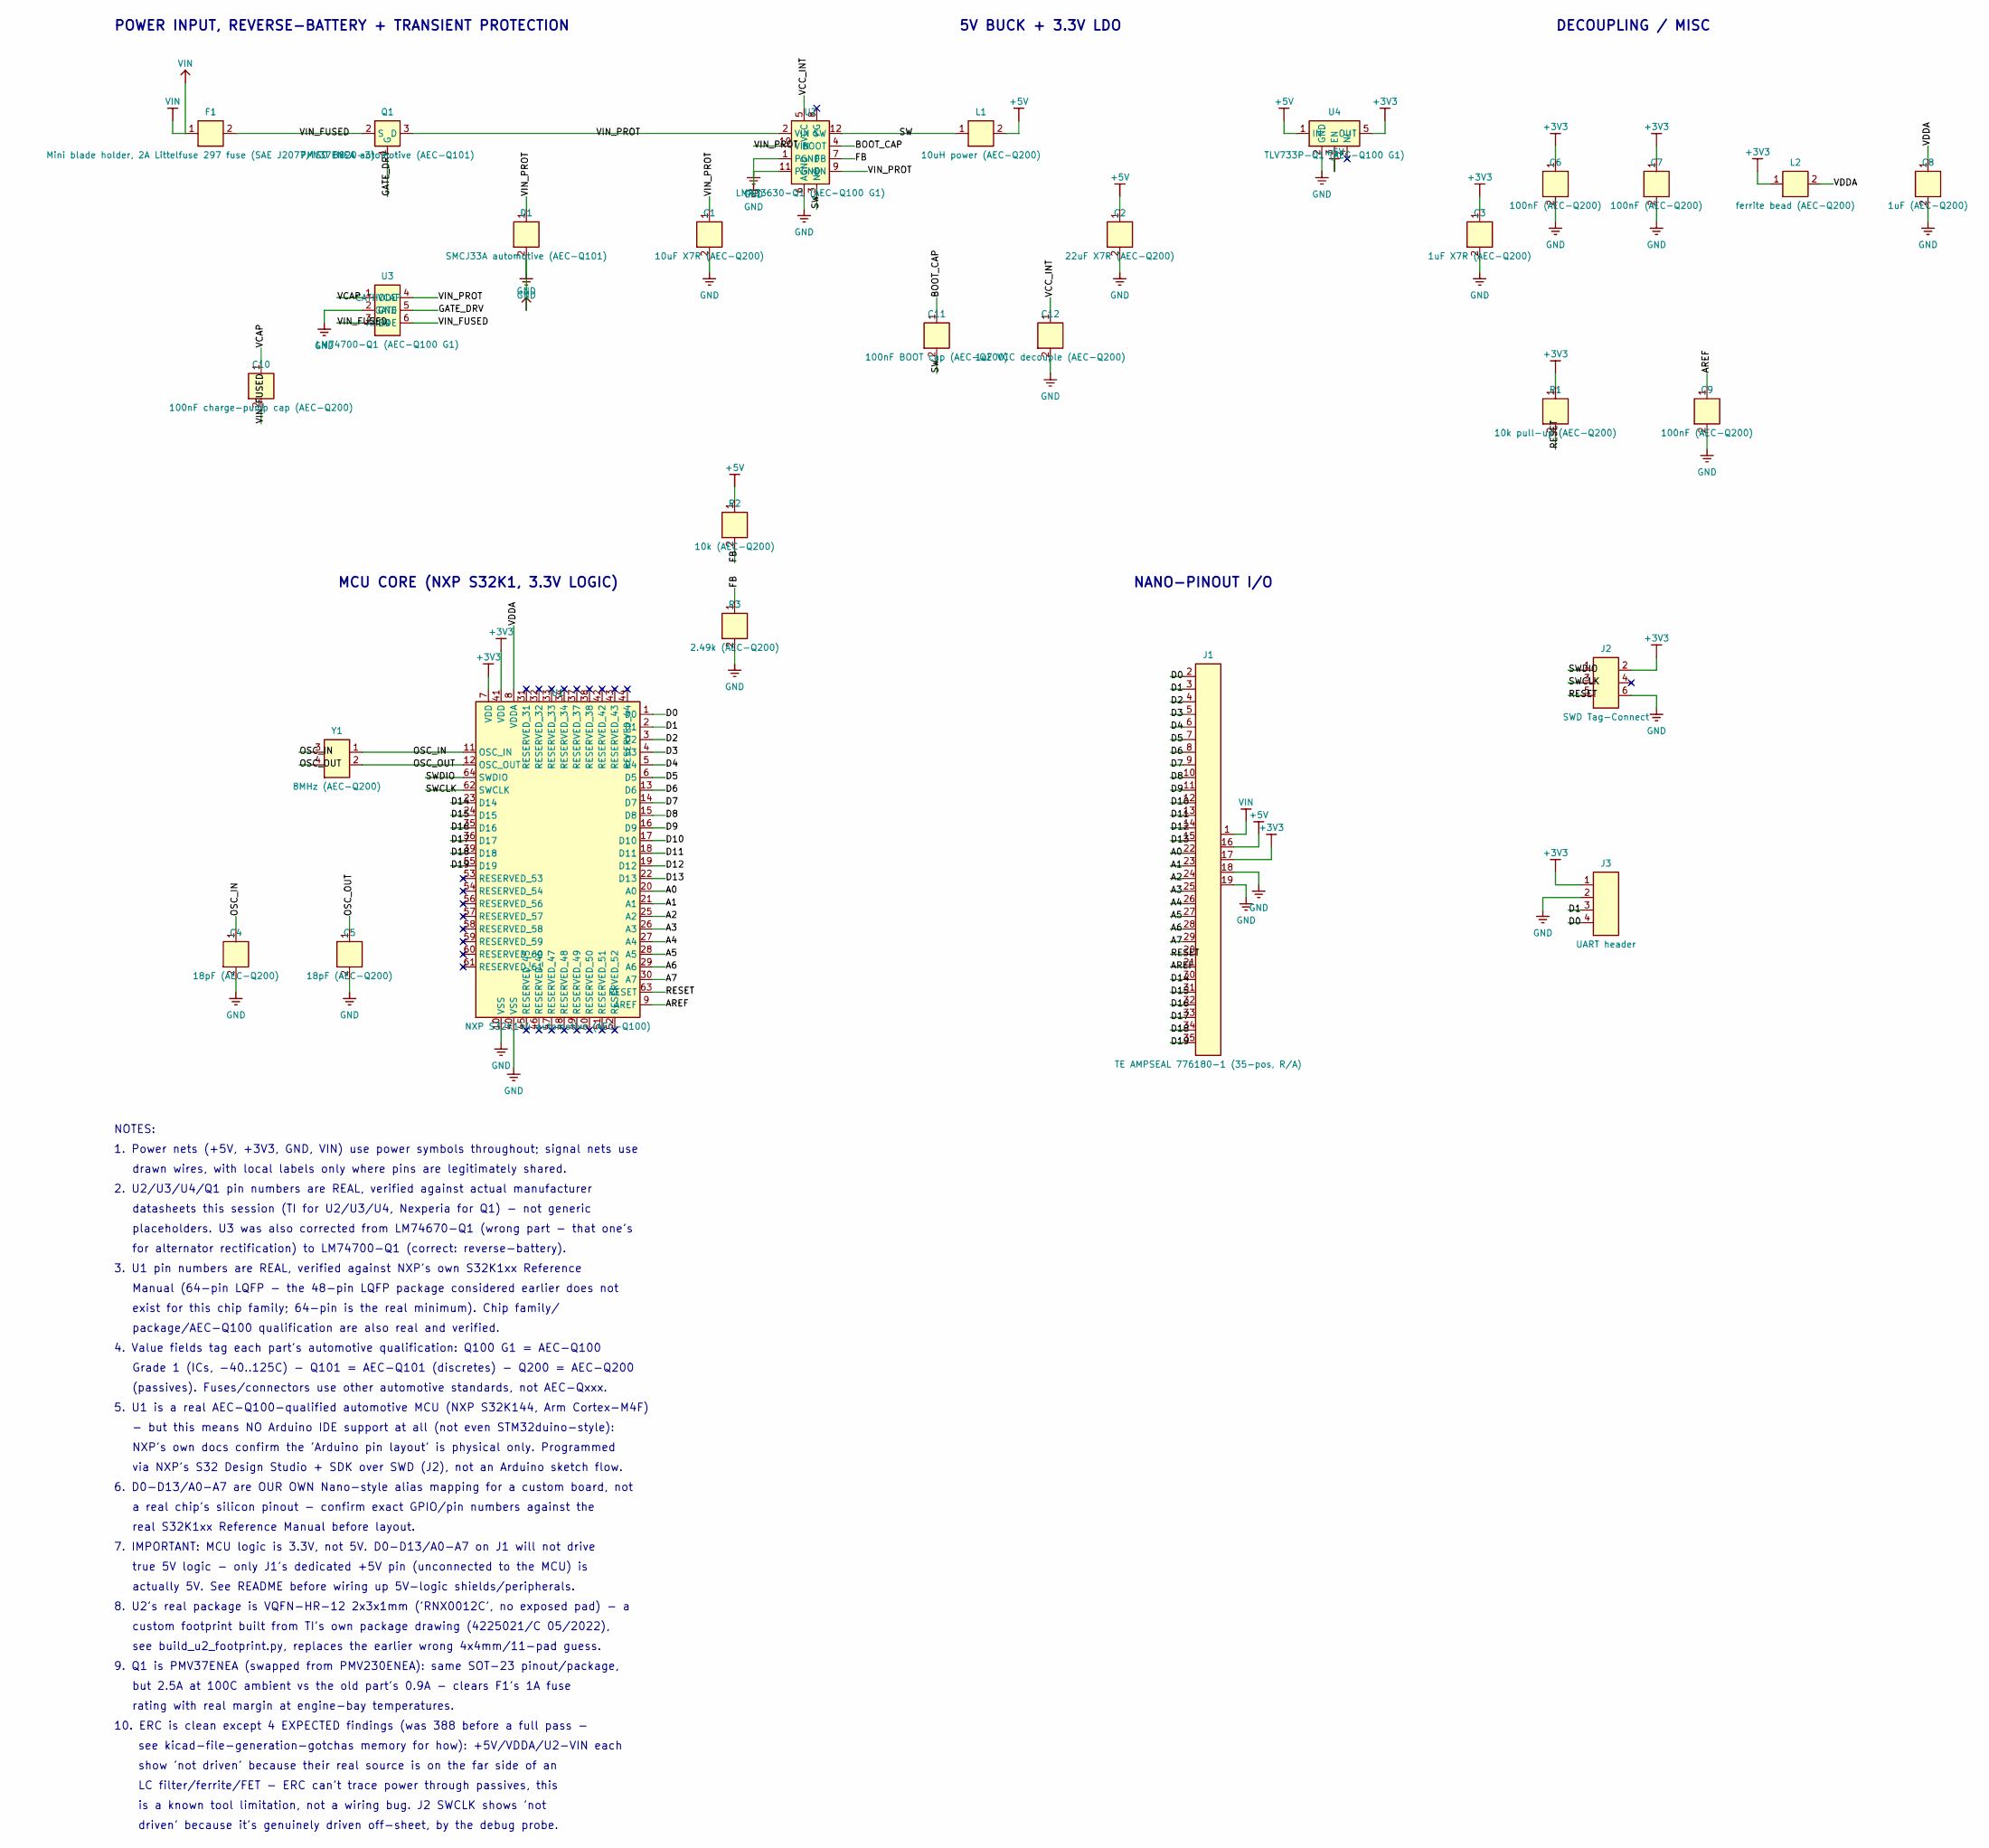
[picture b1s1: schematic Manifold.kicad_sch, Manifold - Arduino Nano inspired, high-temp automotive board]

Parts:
C1: 10uF X7R (AEC-Q200); C_0603_1608Metric
C2: 22uF X7R (AEC-Q200); C_0603_1608Metric
C3: 1uF X7R (AEC-Q200); C_0603_1608Metric
C4, C5: 18pF (AEC-Q200); C_0603_1608Metric
C6, C7, C9: 100nF (AEC-Q200); C_0603_1608Metric
C8: 1uF (AEC-Q200); C_0603_1608Metric
C10: 100nF charge-pump cap (AEC-Q200); C_0603_1608Metric
C11: 100nF BOOT cap (AEC-Q200); C_0603_1608Metric
C12: 1uF VCC decouple (AEC-Q200); C_0603_1608Metric
D1: SMCJ33A automotive (AEC-Q101); D_SMC
F1: Mini blade holder, 2A Littelfuse 297 fuse (SAE J2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; Fuseholder_Blade_Mini_Keystone_3568
J1: TE AMPSEAL 776180-1 (35-pos, R/A); TE_1-776180-1
J2: SWD Tag-Connect; Tag-Connect_TC2030-IDC-NL_2x03_P1.27mm_Vertical
J3: UART header; PinHeader_1x04_P2.54mm_Vertical
L1: 10uH power (AEC-Q200); L_1210_3225Metric
L2: ferrite bead (AEC-Q200); L_1210_3225Metric
Q1: PMV37ENEA automotive (AEC-Q101); SOT-23
R1: 10k pull-up (AEC-Q200); R_0603_1608Metric
R2: 10k (AEC-Q200); R_0603_1608Metric
R3: 2.49k (AEC-Q200); R_0603_1608Metric
U1: NXP S32K144 automotive (AEC-Q100); LQFP-64_10x10mm_P0.5mm
U2: LMR33630-Q1 (AEC-Q100 G1); TI_RNX0012C_VQFN-HR-12_2x3mm_P0.5mm
U3: LM74700-Q1 (AEC-Q100 G1); SOT-23-6
U4: TLV733P-Q1 (AEC-Q100 G1); SOT-23-5
Y1: 8MHz (AEC-Q200); Crystal_SMD_3225-4Pin_3.2x2.5mm

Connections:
+3V3: C3.1, C6.1, C7.1, J1.17 (+3V3), J2.2 (VCC), J3.1 (VCC), L2.1, R1.1, U1.7 (VDD), U1.41 (VDD), U4.5 (OUT)
+5V: C2.1, J1.16 (+5V), L1.2, R2.1, U4.1 (IN), U4.3 (EN)
A0: J1.22 (A0), U1.20 (A0)
A1: J1.23 (A1), U1.21 (A1)
A2: J1.24 (A2), U1.25 (A2)
A3: J1.25 (A3), U1.26 (A3)
A4: J1.26 (A4), U1.27 (A4)
A5: J1.27 (A5), U1.28 (A5)
A6: J1.28 (A6), U1.29 (A6)
A7: J1.29 (A7), U1.30 (A7)
AREF: C9.1, J1.21 (AREF), U1.9 (AREF)
BOOT_CAP: C11.1, U2.4 (BOOT)
D0: J1.2 (D0), J3.4 (RX), U1.1 (D0)
D1: J1.3 (D1), J3.3 (TX), U1.2 (D1)
D2: J1.4 (D2), U1.3 (D2)
D3: J1.5 (D3), U1.4 (D3)
D4: J1.6 (D4), U1.5 (D4)
D5: J1.7 (D5), U1.6 (D5)
D6: J1.8 (D6), U1.13 (D6)
D7: J1.9 (D7), U1.14 (D7)
D8: J1.10 (D8), U1.15 (D8)
D9: J1.11 (D9), U1.16 (D9)
D10: J1.12 (D10), U1.17 (D10)
D11: J1.13 (D11), U1.18 (D11)
D12: J1.14 (D12), U1.19 (D12)
D13: J1.15 (D13), U1.22 (D13)
D14: J1.30 (D14), U1.23 (D14)
D15: J1.31 (D15), U1.24 (D15)
D16: J1.32 (D16), U1.35 (D16)
D17: J1.33 (D17), U1.36 (D17)
D18: J1.34 (D18), U1.39 (D18)
D19: J1.35 (D19), U1.55 (D19)
FB: R2.2, R3.1, U2.7 (FB)
GATE_DRV: Q1.1 (G), U3.5 (GATE)
GND: C1.2, C2.2, C3.2, C4.2, C5.2, C6.2, C7.2, C8.2, C9.2, C12.2, D1.2, J1.18 (GND), J1.19 (GND), J2.6 (GND), J3.2 (GND), R3.2, U1.10 (VSS), U1.40 (VSS), U2.1 (PGND), U2.6 (AGND), U2.11 (PGND), U3.2 (GND), U4.2 (GND)
OSC_IN: C4.1, U1.11 (OSC_IN), Y1.1 (OSC_IN), Y1.3 (OSC_IN)
OSC_OUT: C5.1, U1.12 (OSC_OUT), Y1.2 (OSC_OUT), Y1.4 (OSC_OUT)
RESET: J1.20 (RESET), J2.5 (RST), R1.2, U1.63 (RESET)
SW: C11.2, L1.1, U2.3 (NC), U2.12 (SW)
SWCLK: J2.3 (SWCLK), U1.62 (SWCLK)
SWDIO: J2.1 (SWDIO), U1.64 (SWDIO)
VCAP: C10.1, U3.1 (VCAP)
VCC_INT: C12.1, U2.5 (VCC)
VDDA: C8.1, L2.2, U1.8 (VDDA)
VIN: F1.1, J1.1 (VIN)
VIN_FUSED: C10.2, F1.2, Q1.2 (S), U3.3 (EN), U3.6 (ANODE)
VIN_PROT: C1.1, D1.1, Q1.3 (D), U2.2 (VIN), U2.9 (EN), U2.10 (VIN), U3.4 (CATHODE)

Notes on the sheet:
placeholders. U3 was also corrected from LM74670-Q1 (wrong part - that one's
show 'not driven' because their real source is on the far side of an
NANO-PINOUT I/O
exist for this chip family; 64-pin is the real minimum). Chip family/
6. D0-D13/A0-A7 are OUR OWN Nano-style alias mapping for a custom board, not
DECOUPLING / MISC
8. U2's real package is VQFN-HR-12 2x3x1mm ('RNX0012C', no exposed pad) - a
4. Value fields tag each part's automotive qualification: Q100 G1 = AEC-Q100
but 2.5A at 100C ambient vs the old part's 0.9A - clears F1's 1A fuse
a real chip's silicon pinout - confirm exact GPIO/pin numbers against the
5V BUCK + 3.3V LDO
true 5V logic - only J1's dedicated +5V pin (unconnected to the MCU) is
- but this means NO Arduino IDE support at all (not even STM32duino-style):
drawn wires, with local labels only where pins are legitimately shared.
driven' because it's genuinely driven off-sheet, by the debug probe.
3. U1 pin numbers are REAL, verified against NXP's own S32K1xx Reference
NOTES:
10. ERC is clean except 4 EXPECTED findings (was 388 before a full pass -
is a known tool limitation, not a wiring bug. J2 SWCLK shows 'not
for alternator rectification) to LM74700-Q1 (correct: reverse-battery).
(passives). Fuses/connectors use other automotive standards, not AEC-Qxxx.
real S32K1xx Reference Manual before layout.
via NXP's S32 Design Studio + SDK over SWD (J2), not an Arduino sketch flow.
1. Power nets (+5V, +3V3, GND, VIN) use power symbols throughout; signal nets use
actually 5V. See README before wiring up 5V-logic shields/peripherals.
9. Q1 is PMV37ENEA (swapped from PMV230ENEA): same SOT-23 pinout/package,
datasheets this session (TI for U2/U3/U4, Nexperia for Q1) - not generic
2. U2/U3/U4/Q1 pin numbers are REAL, verified against actual manufacturer
package/AEC-Q100 qualification are also real and verified.
Grade 1 (ICs, -40..125C) - Q101 = AEC-Q101 (discretes) - Q200 = AEC-Q200
MCU CORE (NXP S32K1, 3.3V LOGIC)
POWER INPUT, REVERSE-BATTERY + TRANSIENT PROTECTION
see kicad-file-generation-gotchas memory for how): +5V/VDDA/U2-VIN each
Manual (64-pin LQFP - the 48-pin LQFP package considered earlier does not
LC filter/ferrite/FET - ERC can't trace power through passives, this
custom footprint built from TI's own package drawing (4225021/C 05/2022),
see build_u2_footprint.py, replaces the earlier wrong 4x4mm/11-pad guess.
rating with real margin at engine-bay temperatures.
NXP's own docs confirm the 'Arduino pin layout' is physical only. Programmed
7. IMPORTANT: MCU logic is 3.3V, not 5V. D0-D13/A0-A7 on J1 will not drive

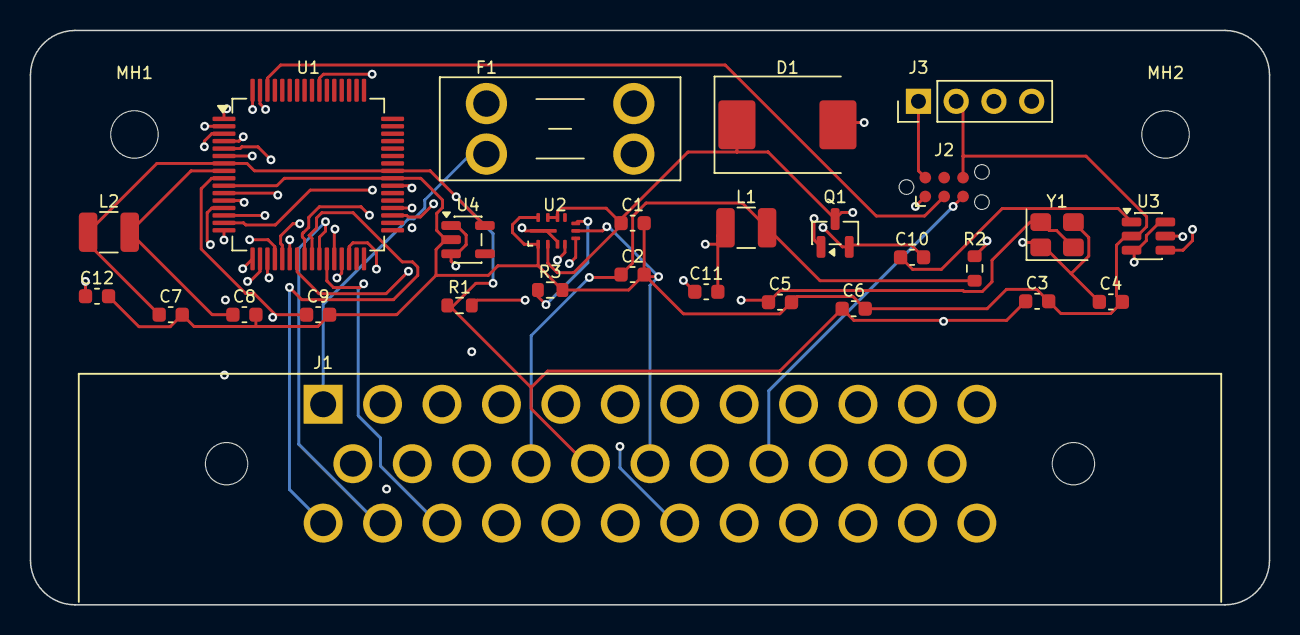
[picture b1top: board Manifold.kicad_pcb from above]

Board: 4 copper layers, 83.4 x 38.7 mm, 30 parts (0 on the bottom side), 47 nets.

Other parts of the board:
MH1, MH2: MountingHole_3.2mm_M3

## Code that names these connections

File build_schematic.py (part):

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      conn={'1': ('pwr', 'VIN'), '2': ('wire',)})
place(f"{LIB}:MOSFET_N", "Q1", "PMV37ENEA automotive (AEC-Q101)", 85, RAIL,
      conn={'2': ('wire',), '3': ('wire',),
            '1': ('label', 'GATE_DRV', 7.62)})
# LM74700-Q1: real pins verified against TI's datasheet. ANODE=battery-side
# (same net as Q1's Source), CATHODE=downstream-side (same net as Q1's
# Drain), EN tied to ANODE for always-on, VCAP needs an external charge-pump
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# to PMV37ENEA (see that symbol's registration comment) - still 0.1uF either
# way, since both parts' Ciss is tiny next to the flat minimum.
place(f"{LIB}:IC_IdealDiode", "U3", "LM74700-Q1 (AEC-Q100 G1)", 85, 85,
      conn={'6': ('label', 'VIN_FUSED', 5.08),
            # GND's stub MUST differ from pin 3's (both on the 'L' side, pin 3
            # directly below pin 2) - the GND riser continues one more PITCH
            # in the same direction pin 3's own stub already reaches, and a
            # matching length would land both on the same point, silently
            # shorting EN's "VIN_FUSED" label onto GND. Confirmed via netlist
            # diff during verification - don't reuse 5.08 here.
            '2': ('pwr', 'GND', 7.62),
            '5': ('label', 'GATE_DRV', 5.08), '4': ('label', 'VIN_PROT', 5.08),
            '3': ('label', 'VIN_FUSED', 5.08), '1': ('label', 'VCAP', 5.08)})
place(f"{LIB}:C_V", "C10", "100nF charge-pump cap (AEC-Q200)", 60, 100,
      conn={'1': ('label', 'VCAP'), '2': ('label', 'VIN_FUSED')})
place(f"{LIB}:TVS_V", "D1", "SMCJ33A automotive (AEC-Q101)", 113, 70,
      conn={'1': ('label', 'VIN_PROT'), '2': ('pwr', 'GND')})
place(f"{LIB}:C_V", "C1", "10uF X7R (AEC-Q200)", 150, 70,
      conn={'1': ('label', 'VIN_PROT'), '2': ('pwr', 'GND')})

# VIN and GND both come from off-sheet (the battery, via J1) with nothing
# HERE electrically "driving" them, per ERC - a real PWR_FLAG (not a supply
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# needs its own decoupling cap, PG (power-good) unused here.
y_u2 = RAIL - off(f"{LIB}:IC_Buck", 2)[1]      # align U2 pin 2 (VIN) with the rail
place(f"{LIB}:IC_Buck", "U2", "LMR33630-Q1 (AEC-Q100 G1)", 170, y_u2,
      conn={'2': ('wire',), '10': ('label', 'VIN_PROT', 5.08),
            '1': ('pwr', 'GND', 5.08), '11': ('pwr', 'GND', 5.08),
            '12': ('wire',), '4': ('label', 'BOOT_CAP'),
            '7': ('label', 'FB'), '9': ('label', 'VIN_PROT', 5.08),
            '5': ('label', 'VCC_INT'), '8': ('nc',),
            '6': ('pwr', 'GND'), '3': ('label', 'SW')})
place(f"{LIB}:C_V", "C11", "100nF BOOT cap (AEC-Q200)", 195, 90,
      conn={'1': ('label', 'BOOT_CAP'), '2': ('label', 'SW')})
place(f"{LIB}:C_V", "C12", "1uF VCC decouple (AEC-Q200)", 218, 90,
      conn={'1': ('label', 'VCC_INT'), '2': ('pwr', 'GND')})
y_l1 = pin_pos[("U2", "12")][1] - off(f"{LIB}:L_H", 1)[1]
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      conn={'1': ('pwr', '+3V3'), '2': ('pwr', 'GND')})

# rail wires
wire_pins("F1", 2, "Q1", 2, label="VIN_FUSED")
wire_pins("Q1", 3, "U2", 2, label="VIN_PROT")
wire_pins("U2", 12, "L1", 1, label="SW")

# --- MCU core + I/O bus ---
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y_y1 = pin_pos[("U1", "11")][1] - off(f"{LIB}:XTAL", 1)[1]
place(f"{LIB}:XTAL", "Y1", "8MHz (AEC-Q200)", 75, y_y1,
      conn={'1': ('wire',), '2': ('wire',),
            '3': ('label', 'OSC_IN'), '4': ('label', 'OSC_OUT')})
wire_pins("Y1", 1, "U1", 11, label="OSC_IN")
wire_pins("Y1", 2, "U1", 12, label="OSC_OUT")
place(f"{LIB}:C_V", "C4", "18pF (AEC-Q200)", 55, y_y1 + 40,
      conn={'1': ('label', 'OSC_IN'), '2': ('pwr', 'GND')})
place(f"{LIB}:C_V", "C5", "18pF (AEC-Q200)", 78, y_y1 + 40,
      conn={'1': ('label', 'OSC_OUT'), '2': ('pwr', 'GND')})

# --- decoupling / misc, top right --- (VDD/VDDA now +3V3, not +5V)
place(f"{LIB}:C_V", "C6", "100nF (AEC-Q200)", 320, 60,
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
